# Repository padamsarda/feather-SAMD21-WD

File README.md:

# Feather SAMD21 MAX637X Watchdog dev board

A Feather-compatible development board based on the ATSAMD21G18A microcontroller with an integrated MAX6373 hardware watchdog for improving system reliability. The board retains the Adafruit Feather M0 Express footprint and pinout while incorporating USB Type-C connectivity, Li-Po battery charging, USB protection, and external clock circuitry. A 555 monostable circuit enables MCU power cycling, while multiple jumper options allow sections of the watchdog and reset circuitry to be enabled, disabled, or bypassed as required.

### Board at a glance

| Category | Hardware |
|----------|----------|
| MCU | ATSAMD21G18A |
| Hardware Watchdog | MAX6373 |
| USB | USB Type-C with USBLC6-2SC6 ESD protection |
| Battery Charging | MCP73832 |
| Voltage Regulation | AP2112K-3.3 (×2), LM5155xMM |
| Clock | 32.768 kHz crystal oscillator |
| Power Cycling | 555 monostable circuit |
| Expansion | Feather-compatible headers |

## MCU-WD Architecture

<p align="center">
  <br>
  <em>High-level architecture of the Feather SAMD21 Watchdog board.</em>
</p>

## Schematic

## PCB

## Key Components

| Reference | Part | Function |
|----------|------|----------|
| U3 | ATSAMD21G18A-MU | Main microcontroller |
| U8 | MAX6373 | Hardware watchdog supervisor |
| U5 | MCP73832 | Li-Po battery charger |
| U2 | USBLC6-2SC6 | USB ESD protection |
| U4, U6 | AP2112K-3.3 | 3.3 V regulators |
| U7 | LM5155xMM | Power regulation |
| X1 | 32.768 kHz Crystal | External RTC clock source |
| D3 | BAT43W | Schottky diode |
| D2 | LED | Status indication |

## Connectors & I/O

| Reference | Interface | Description |
|----------|-----------|-------------|
| J1 | JumperSET0 | Watchdog configuration |
| J2 | JumperSET1 | Watchdog configuration |
| J3 | JumperSET2 | Watchdog configuration |
| J4 | Left Feather Header | Feather-compatible expansion |
| J5 | Right Feather Header | Feather-compatible expansion |
| J6 | Battery Header | Li-Po battery connection |
| J7 | Reset Enable Jumper | Enable/disable reset path |
| J8 | USB Type-C | USB interface |
| J9 | WD_PWR Jumper | Watchdog power control |
| J10 | Monostable Bypass Jumper | Bypass 555 power-cycle circuit |

Designed and developed as part of **Team Anant**.

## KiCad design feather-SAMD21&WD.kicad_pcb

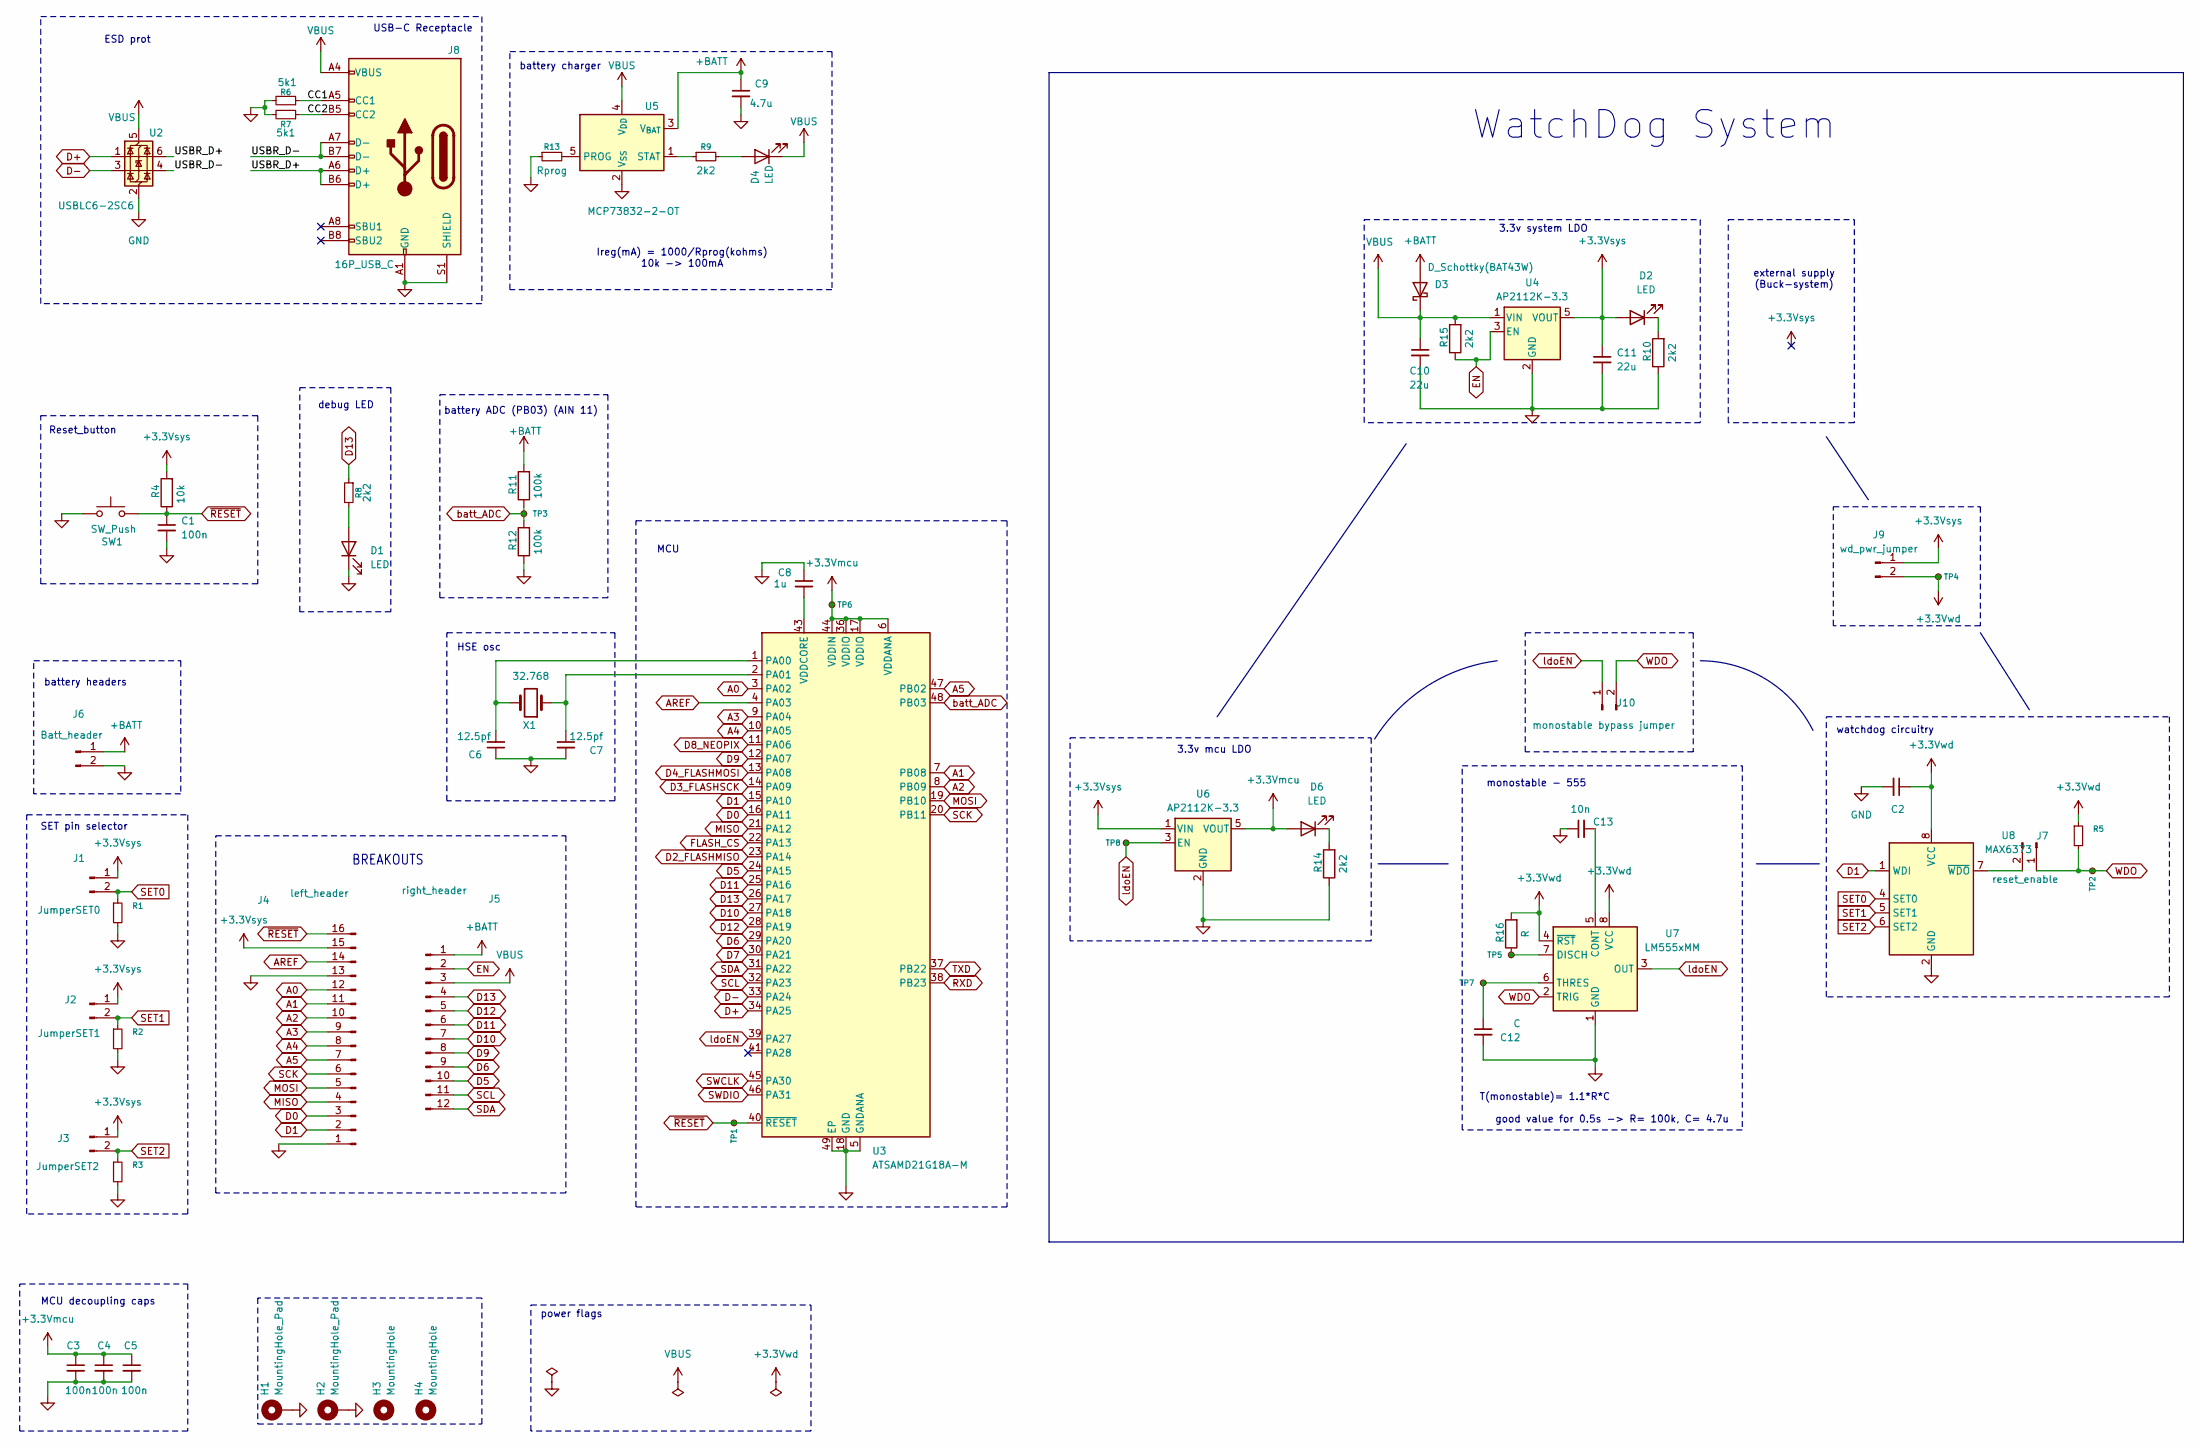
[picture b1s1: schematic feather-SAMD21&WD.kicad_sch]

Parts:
C1, C2, C3, C4, C5: 100n; C_0805_2012Metric_Pad1.18x1.45mm_HandSolder
C6, C7: 12.5pf; C_0805_2012Metric_Pad1.18x1.45mm_HandSolder
C8: 1u; C_0805_2012Metric_Pad1.18x1.45mm_HandSolder
C9: 4.7u; C_0805_2012Metric_Pad1.18x1.45mm_HandSolder
C10, C11: 22u; C_0805_2012Metric_Pad1.18x1.45mm_HandSolder
C12: C; C_0805_2012Metric_Pad1.18x1.45mm_HandSolder
C13: 10n; C_0805_2012Metric_Pad1.18x1.45mm_HandSolder
D1, D4: LED; LED_0805_2012Metric
D2, D6: LED; LED_0805_2012Metric_Pad1.15x1.40mm_HandSolder
D3: D_Schottky(BAT43W); D_SOD-123
H1, H2: MountingHole_Pad; feather_mounting hole M2.5
H3, H4: MountingHole; feather_mounting hole (no pad)
J1: JumperSET0; SolderJumper-2_P1.3mm_Open_RoundedPad1.0x1.5mm
J2: JumperSET1; SolderJumper-2_P1.3mm_Open_RoundedPad1.0x1.5mm
J3: JumperSET2; SolderJumper-2_P1.3mm_Open_RoundedPad1.0x1.5mm
J4: left_header; PinHeader_1x16_P2.54mm_Vertical
J5: right_header; PinHeader_1x12_P2.54mm_Vertical
J6: Batt_header; PinHeader_1x02_P2.54mm_Vertical
J7: reset_enable; SolderJumper-2_P1.3mm_Open_RoundedPad1.0x1.5mm
J8: 16P_USB_C; USB_C_Receptacle_G-Switch_GT-USB-7010ASV
J9: wd_pwr_jumper; SolderJumper-2_P1.3mm_Open_RoundedPad1.0x1.5mm
J10: monostable bypass jumper; SolderJumper-2_P1.3mm_Open_Pad1.0x1.5mm
R1, R2, R3, R5: R_Small; R_0805_2012Metric_Pad1.20x1.40mm_HandSolder
R4: 10k; R_0805_2012Metric_Pad1.20x1.40mm_HandSolder
R6, R7: 5k1; R_0805_2012Metric_Pad1.20x1.40mm_HandSolder
R8, R9, R10, R14, R15: 2k2; R_0805_2012Metric_Pad1.20x1.40mm_HandSolder
R11, R12: 100k; R_0805_2012Metric_Pad1.20x1.40mm_HandSolder
R13: Rprog; R_0805_2012Metric_Pad1.20x1.40mm_HandSolder
R16: R; R_0805_2012Metric_Pad1.20x1.40mm_HandSolder
SW1: SW_Push; tactile switch 4.5_4.5
TP1, TP2, TP3, TP4, TP5, TP6, TP7, TP8: TestPoint_Small; TestPoint_Pad_D1.5mm
U2: USBLC6-2SC6; SOT-23-6
U3: ATSAMD21G18A-M; QFN-48-1EP_7x7mm_P0.5mm_EP5.15x5.15mm
U4, U6: AP2112K-3.3; SOT-23-5
U5: MCP73832-2-OT; SOT-23-5
U7: LM555xMM; VSSOP-8_3x3mm_P0.65mm
U8: MAX6373; SOT-23-8
X1: 32.768; Crystal_SMD_3215-2Pin_3.2x1.5mm

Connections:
+3.3Vmcu: C3.1, C4.1, C5.1, D6.2 (A), TP6.1 (1_1), U3.6 (VDDANA), U3.17 (VDDIO), U3.36 (VDDIO), U3.44 (VDDIN), U6.5 (VOUT)
+3.3Vsys: C11.1, D2.2 (A), J1.1, J2.1, J3.1, J4.15, J9.1, R4.2, U4.5 (VOUT), U6.1 (VIN)
+3.3Vwd: C2.1, J9.2, R5.1, R16.2, TP4.1 (1_1), U7.4 (~RST), U7.8 (VCC), U8.8 (VCC); also elsewhere on the board
+BATT: C9.1, D3.2 (A), J5.1, J6.1, R11.2, U5.3 (V_{BAT})
/CC1: J8.A5 (CC1), R6.1
/CC2: J8.B5 (CC2), R7.1
/USBR_D+: J8.A6 (D+), J8.B6 (D+), U2.6 (I/O1)
/USBR_D-: J8.A7 (D-), J8.B7 (D-), U2.4 (I/O2)
A0: J4.12, U3.3 (PA02)
A1: J4.11, U3.7 (PB08)
A2: J4.10, U3.8 (PB09)
A3: J4.9, U3.9 (PA04)
A4: J4.8, U3.10 (PA05)
A5: J4.7, U3.47 (PB02)
AREF: J4.14, U3.4 (PA03)
D0: J4.3, U3.16 (PA11)
D1: J4.2, U3.15 (PA10), U8.1 (WDI); also elsewhere on the board
D2_FLASHMISO: U3.23 (PA14)
D3_FLASHSCK: U3.14 (PA09)
D4_FLASHMOSI: U3.13 (PA08)
D5: J5.10, U3.24 (PA15)
D6: J5.9, U3.29 (PA20)
D7: U3.30 (PA21)
D8_NEOPIX: U3.11 (PA06)
D9: J5.8, U3.12 (PA07)
D10: J5.7, U3.27 (PA18)
D11: J5.6, U3.25 (PA16)
D12: J5.5, U3.28 (PA19)
D13: J5.4, R8.1, U3.26 (PA17)
D+: U2.1 (I/O1), U3.34 (PA25)
D-: U2.3 (I/O2), U3.33 (PA24)
EN: J5.2, R15.1, U4.3 (EN)
FLASH_CS: U3.22 (PA13)
GND: C1.2, C2.2, C3.2, C4.2, C5.2, C6.1, C7.2, C8.1, C9.2, C10.2, C11.2, C12.2, C13.1, D1.1 (K), H1.1 (1_1), H2.1 (1_1), J4.1, J4.13, J6.2, J8.A1 (GND), J8.A12 (GND), J8.B1 (GND), J8.B12 (GND), J8.S1 (SHIELD), R1.2, R2.2, R3.2, R6.2, R7.2, R10.1, R12.1, R13.1, R14.1, SW1.1, U2.2 (GND), U3.5 (GNDANA), U3.18 (GND), U3.35 (GND), U3.42 (GND), U3.49 (EP), U4.2 (GND), U5.2 (V_{SS}), U6.2 (GND), U7.1 (GND), U8.2 (GND); also elsewhere on the board
MISO: J4.4, U3.21 (PA12)
MOSI: J4.5, U3.19 (PB10)
unnamed: D1.2 (A), R8.2
unnamed: D2.1 (K), R10.2
unnamed: D4.2 (A), R9.2
unnamed: D6.1 (K), R14.2
unnamed 40: J7.2, U8.7 (~WDO); also elsewhere on the board
unnamed: C6.2, U3.1 (PA00), X1.2
unnamed: C7.1, U3.2 (PA01), X1.1
unnamed: C8.2, U3.43 (VDDCORE)
unnamed: R13.2, U5.5 (PROG)
unnamed: R9.1, U5.1 (STAT)
unnamed: C13.2, U7.5 (CONT)
unnamed: R16.1, TP5.1 (1_1), U7.7 (DISCH)
unnamed: C12.1, TP7.1 (1_1), U7.6 (THRES)
RXD: U3.38 (PB23)
SCK: J4.6, U3.20 (PB11)
SCL: J5.11, U3.32 (PA23)
SDA: J5.12, U3.31 (PA22)
SET0: J1.2, R1.1, U8.4 (SET0); also elsewhere on the board
SET1: J2.2, R2.1, U8.5 (SET1); also elsewhere on the board
SET2: J3.2, R3.1, U8.6 (SET2); also elsewhere on the board
SWCLK: U3.45 (PA30)
SWDIO: U3.46 (PA31)
TXD: U3.37 (PB22)
VBUS: C10.1, D3.1 (K), D4.1 (K), J5.3, J8.A4 (VBUS), J8.A9 (VBUS), J8.B4 (VBUS), J8.B9 (VBUS), R15.2, U2.5 (VBUS), U4.1 (VIN), U5.4 (V_{DD})
WDO: J7.1, J10.2, R5.2, TP2.1 (1_1), U7.2 (TRIG)
batt_ADC: R11.1, R12.2, TP3.1 (1_1), U3.48 (PB03)
ldoEN: J10.1, TP8.1 (1_1), U3.39 (PA27), U6.3 (EN), U7.3 (OUT)
~RESET: C1.1, J4.16, R4.1, SW1.2, TP1.1 (1_1), U3.40 (~RESET)

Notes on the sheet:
BREAKOUTS
watchdog circuitry
battery ADC (PB03) (AIN 11)
MCU decoupling caps
3.3v system LDO
Reset_button
MCU
HSE osc
power flags
battery headers
3.3v mcu LDO
good value for 0.5s -> R= 100k, C= 4.7u
monostable - 555
battery charger
ESD prot
Ireg(mA) = 1000/Rprog(kohms) 10k -> 100mA
debug LED
T(monostable)= 1.1*R*C
SET pin selector
WatchDog System
USB-C Receptacle
external supply (Buck-system)

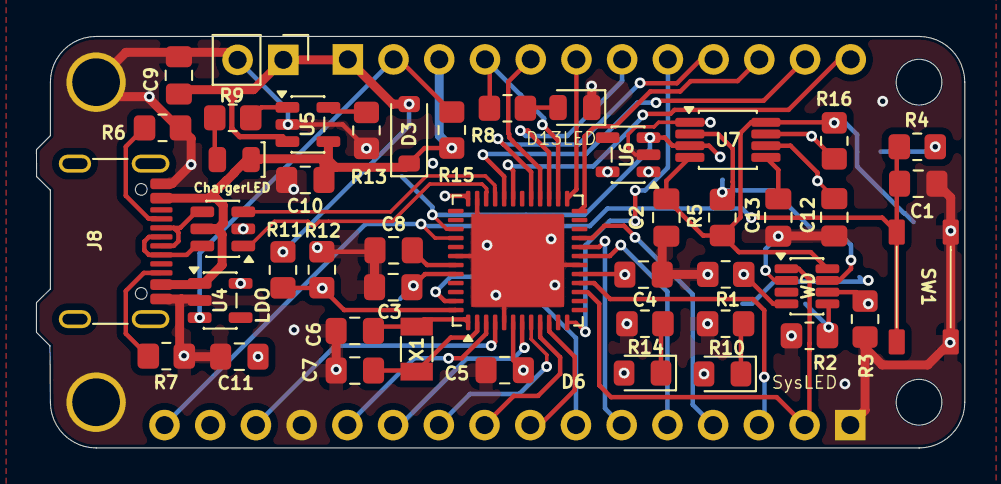
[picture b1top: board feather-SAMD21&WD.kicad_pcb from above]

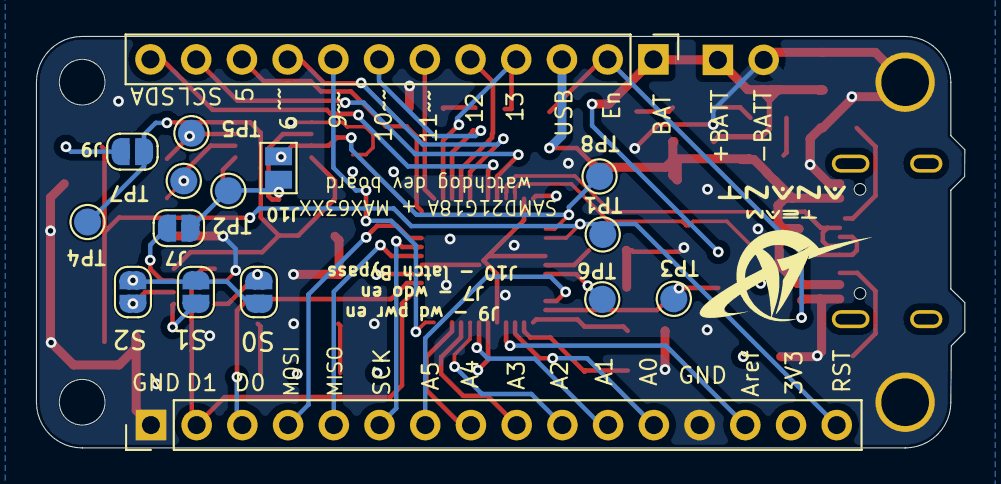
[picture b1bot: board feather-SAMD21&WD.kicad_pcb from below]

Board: 4 copper layers, 51.6 x 22.9 mm, 65 parts (16 on the bottom side), 54 nets.

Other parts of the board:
WD: MAX6373; SOT-23-8

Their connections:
+3.3Vwd: WD.8 (VCC); also elsewhere on the board
D1: WD.1 (WDI); also elsewhere on the board
GND: WD.2 (GND); also elsewhere on the board
unnamed 40: WD.7 (~WDO); also elsewhere on the board
SET0: WD.4 (SET0); also elsewhere on the board
SET1: WD.5 (SET1); also elsewhere on the board
SET2: WD.6 (SET2); also elsewhere on the board
